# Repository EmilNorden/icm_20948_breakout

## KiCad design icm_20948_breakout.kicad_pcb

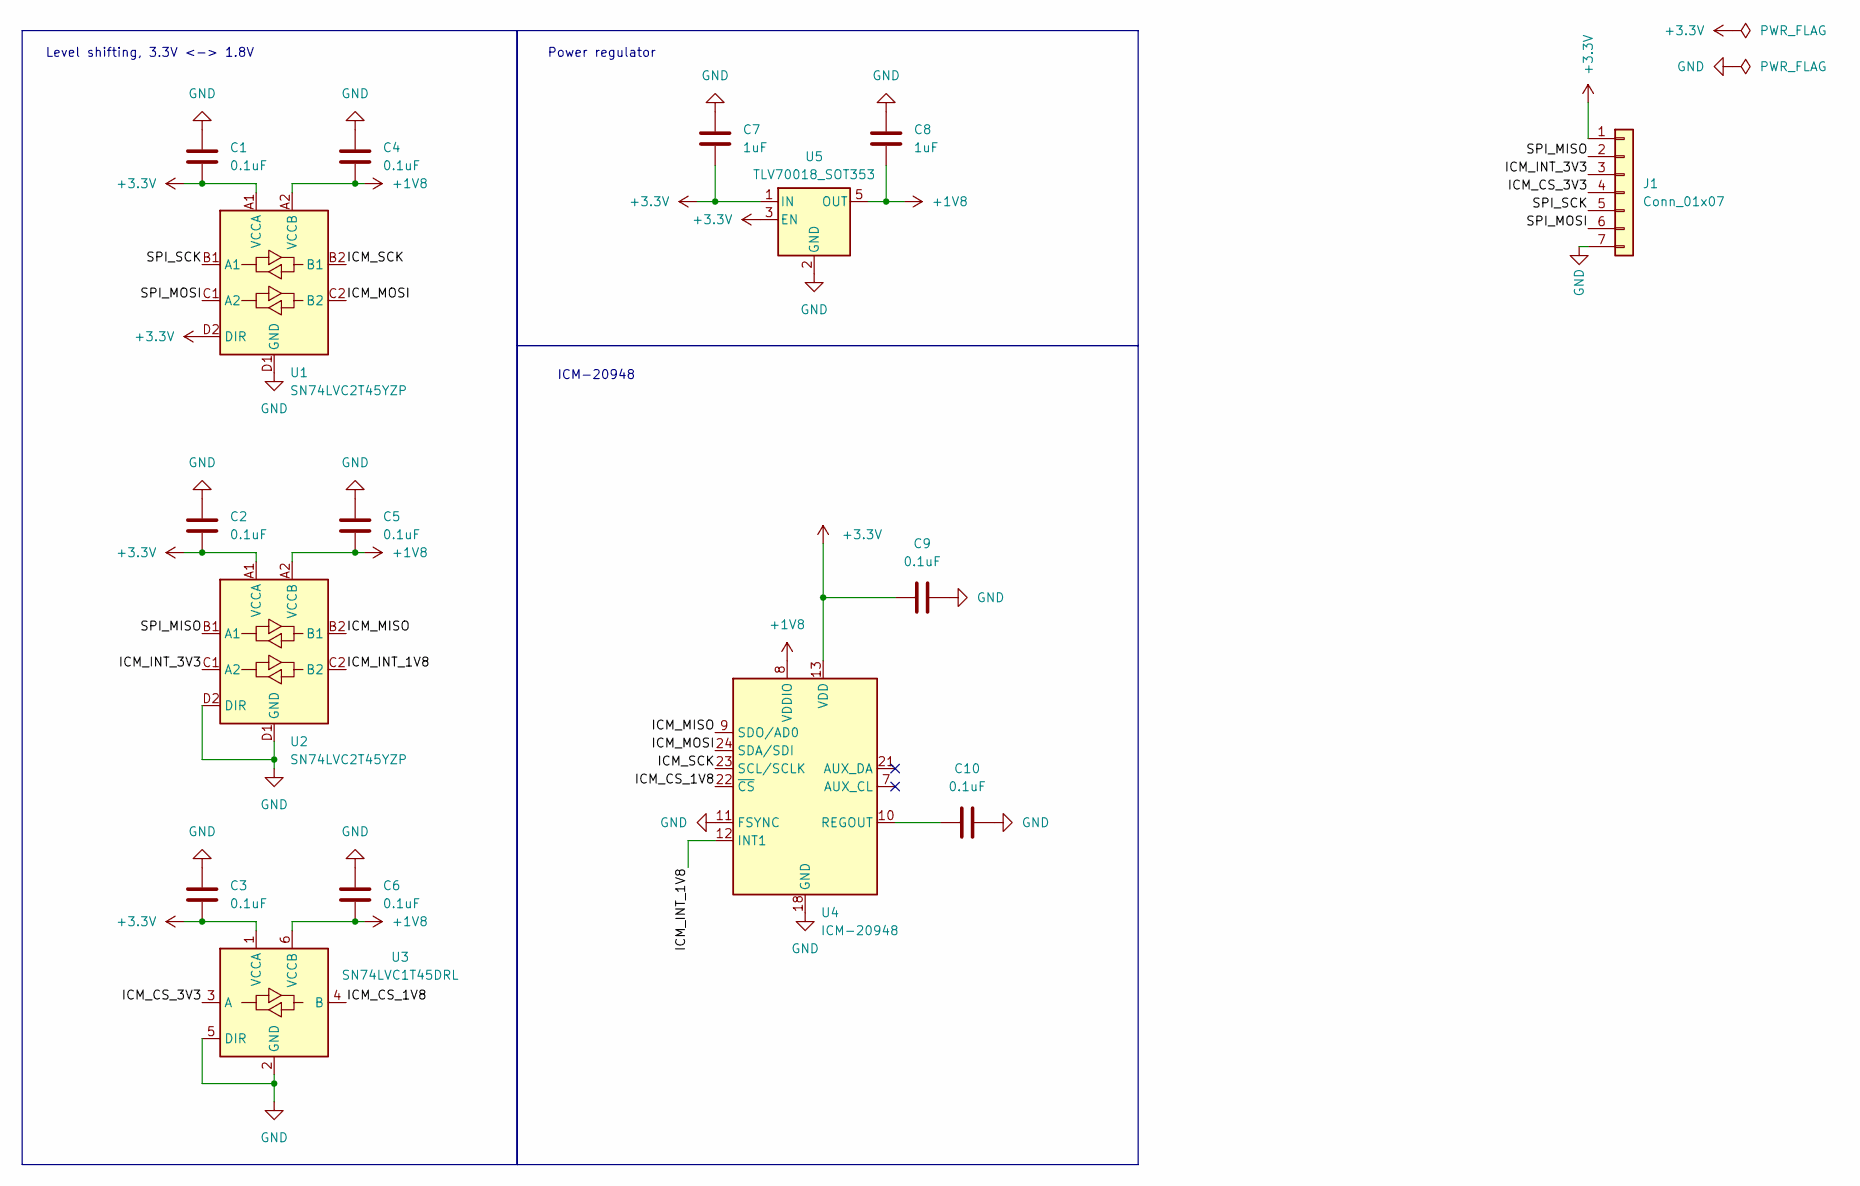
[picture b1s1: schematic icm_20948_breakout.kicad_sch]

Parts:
C1, C2, C3, C4, C5, C6, C9, C10: 0.1uF; C_0402_1005Metric; LCSC C1525
C7, C8: 1uF; C_0402_1005Metric; LCSC C88945
J1: Conn_01x07; PinHeader_1x07_P2.54mm_Vertical; LCSC C492406
U1, U2: SN74LVC2T45YZP; Texas_DSBGA-8_0.9x1.9mm_Layout2x4_P0.5mm; LCSC C913828
U3: SN74LVC1T45DRL; SOT-563; LCSC C352970
U4: ICM-20948; InvenSense_QFN-24_3x3mm_P0.4mm; LCSC C726001
U5: TLV70018_SOT353; SOT-353_SC-70-5; LCSC C133796

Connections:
+1V8: C4.2, C5.2, C6.2, C8.2, U1.A2 (VCCB), U2.A2 (VCCB), U3.6 (VCCB), U4.8 (VDDIO), U5.5 (OUT)
+3.3V: C1.2, C2.2, C3.2, C7.2, C9.1, J1.1, U1.A1 (VCCA), U1.D2 (DIR), U2.A1 (VCCA), U3.1 (VCCA), U4.13 (VDD), U5.1 (IN), U5.3 (EN)
/ICM_CS_1V8: U3.4 (B), U4.22 (~CS)
/ICM_CS_3V3: J1.4, U3.3 (A)
/ICM_INT_1V8: U2.C2 (B2), U4.12 (INT1)
/ICM_INT_3V3: J1.3, U2.C1 (A2)
/ICM_MISO: U2.B2 (B1), U4.9 (SDO/AD0)
/ICM_MOSI: U1.C2 (B2), U4.24 (SDA/SDI)
/ICM_SCK: U1.B2 (B1), U4.23 (SCL/SCLK)
/SPI_MISO: J1.2, U2.B1 (A1)
/SPI_MOSI: J1.6, U1.C1 (A2)
/SPI_SCK: J1.5, U1.B1 (A1)
GND: C1.1, C2.1, C3.1, C4.1, C5.1, C6.1, C7.1, C8.1, C9.2, C10.2, J1.7, U1.D1 (GND), U2.D1 (GND), U2.D2 (DIR), U3.2 (GND), U3.5 (DIR), U4.11 (FSYNC), U4.18 (GND), U4.20 (GND), U5.2 (GND)
unnamed: C10.1, U4.10 (REGOUT)

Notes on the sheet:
Level shifting, 3.3V <-> 1.8V
ICM-20948
Power regulator

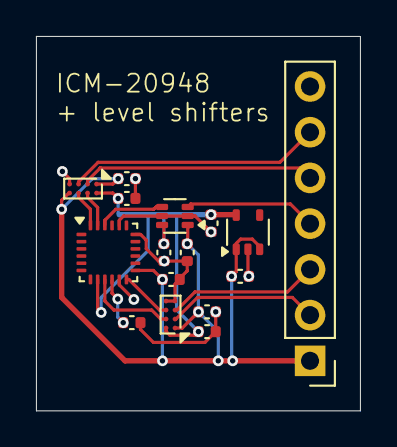
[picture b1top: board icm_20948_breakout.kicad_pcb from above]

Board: 2 copper layers, 18.0 x 20.8 mm, 16 parts (0 on the bottom side), 14 nets.

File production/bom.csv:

Designator,Footprint,Quantity,Value,LCSC Part #
"C1, C10, C2, C3, C4, C5, C6, C9",0402,8,0.1uF,C1525
"C7, C8",0402,2,1uF,C88945
J1,PinHeader_1x07_P2.54mm_Vertical,1,Conn_01x07,C492406
"U1, U2",Texas_DSBGA-8_0.9x1.9mm_Layout2x4_P0.5mm,2,SN74LVC2T45YZP,C913828
U3,SOT-563,1,SN74LVC1T45DRL,C352970
U4,InvenSense_QFN-24_3x3mm_P0.4mm,1,ICM-20948,C726001
U5,SOT-353_SC-70-5,1,TLV70018_SOT353,C133796

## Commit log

2025-09-28 Revised footprints and re-designed PCB
2025-09-29 generated gerbers for v1
2025-09-29 tried out automatic production file generation
2025-09-29 included missing BOM files
2025-09-30 added JLCPCB part numbers
